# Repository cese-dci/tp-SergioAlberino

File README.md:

# tp-SergioAlberino
tp-SergioAlberino created by GitHub Classroom
Materia: Diseño de Circuitos Impresos. Especialización de Sistemas Embebidos (FIUBA)

Poncho distribuidor para Robot rUVot
====================================

Placa para el robot "rUVot". Se trata de un pequeño robot movil para inspección y desinfección por UV. El mismo tiene un funcionamiento autónomo o puede manejarse en modo teleoperado por Bluetooth

La finalidad de esta Placa es la de cumplir funciones de  "distribuidora" de los pines de la EDU-CIA para interconectar los sensores y actuadores del robot de inspección y desinfección por UV. 
Permite conectar todo en forma ordenada y modular. 
El dongle Bluetooth se conecta a esta placa.

URL: (URL en la wiki de la CIAA)
FUNCIÓN: Placa "distribuidora" de los pines de la EDU-CIA para interconectar los sensores y actuadores de un robot de inspección y desinfección por UV

AUTORES/INSTITUCIONES: Sergio Alberino / GIAR - UTN.FRBA

DOCENTE: Diego Brengi

REVISOR: Pablo D. Folino

Año: 2021

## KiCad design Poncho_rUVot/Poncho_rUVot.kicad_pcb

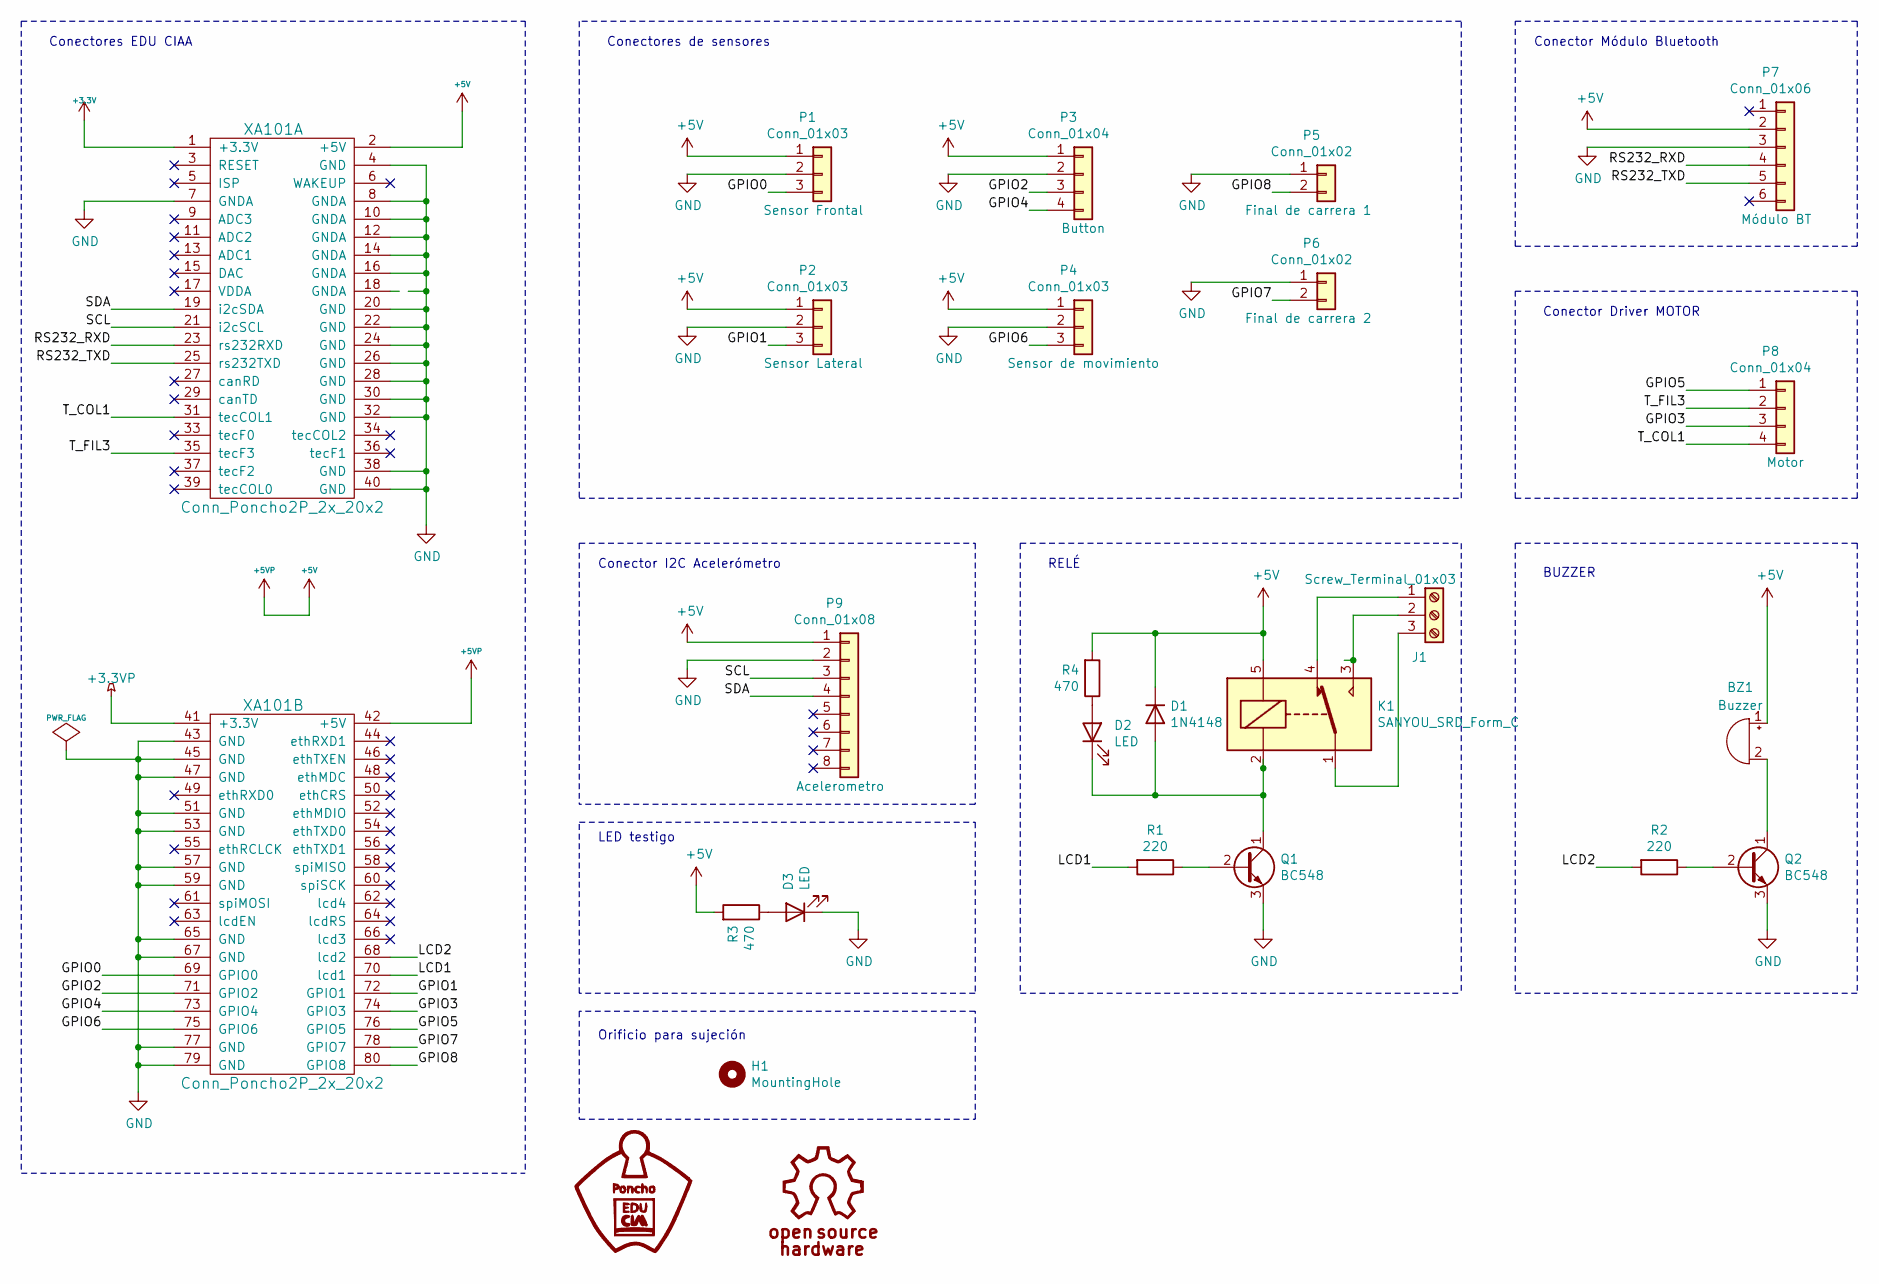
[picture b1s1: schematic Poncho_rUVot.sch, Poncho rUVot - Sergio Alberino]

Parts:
BZ1: Buzzer; Buzzer_12x9.5RM7.6
D1: 1N4148; D_DO-35_SOD27_P10.16mm_Horizontal
D2, D3: LED; LED_D5.0mm
H1: MountingHole; MountingHole_2.5mm
J1: Screw_Terminal_01x03; TerminalBlock_Phoenix_MKDS-1,5-3-5.08_1x03_P5.08mm_Horizont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
K1: SANYOU_SRD_Form_C; Relay_SPDT_SANYOU_SRD_Series_Form_C
P1, P2, P4: Conn_01x03; PinHeader_1x03_P2.54mm_Horizontal
P3: Conn_01x04; PinHeader_1x04_P2.54mm_Horizontal
P5, P6: Conn_01x02; PinHeader_1x02_P2.54mm_Horizontal
P7: Conn_01x06; PinSocket_1x06_P2.54mm_Vertical
P8: Conn_01x04; PinHeader_1x04_P2.54mm_Vertical
P9: Conn_01x08; PinSocket_1x08_P2.54mm_Vertical
Q1, Q2: BC548; TO-92L_Wide
R1, R2: 220; R_Axial_DIN0204_L3.6mm_D1.6mm_P7.62mm_Horizontal
R3, R4: 470; R_Axial_DIN0204_L3.6mm_D1.6mm_P7.62mm_Horizontal
XA101: Conn_Poncho2P_2x_20x2; Conn_Poncho_SinBorde; Digikey# 952-1387-ND

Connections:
+3.3VP: XA101.41 (+3.3V)
+3V3: XA101.1 (+3.3V)
+5V: BZ1.1 (-), D1.1 (K), K1.5, P1.1, P2.1, P3.1, P4.1, P7.2, P9.1, R3.2, R4.2, XA101.2 (+5V), XA101.42 (+5V)
/GPIO0: P1.3, XA101.69 (GPIO0)
/GPIO1: P2.3, XA101.72 (GPIO1)
/GPIO2: P3.3, XA101.71 (GPIO2)
/GPIO3: P8.3, XA101.74 (GPIO3)
/GPIO4: P3.4, XA101.73 (GPIO4)
/GPIO5: P8.1, XA101.76 (GPIO5)
/GPIO6: P4.3, XA101.75 (GPIO6)
/GPIO7: P6.2, XA101.78 (GPIO7)
/GPIO8: P5.2, XA101.80 (GPIO8)
/LCD1: R1.2, XA101.70 (lcd1)
/LCD2: R2.2, XA101.68 (lcd2)
/RS232_RXD: P7.4, XA101.23 (rs232RXD)
/RS232_TXD: P7.5, XA101.25 (rs232TXD)
/SCL: P9.3, XA101.21 (i2cSCL)
/SDA: P9.4, XA101.19 (i2cSDA)
/T_COL1: P8.4, XA101.31 (tecCOL1)
/T_FIL3: P8.2, XA101.35 (tecF3)
GND: D3.1 (K), P1.2, P2.2, P3.2, P4.2, P5.1, P6.1, P7.3, P9.2, Q1.3 (E), Q2.3 (E), XA101.4 (GND), XA101.7 (GNDA), XA101.8 (GNDA), XA101.10 (GNDA), XA101.12 (GNDA), XA101.14 (GNDA), XA101.16 (GNDA), XA101.20 (GND), XA101.22 (GND), XA101.24 (GND), XA101.26 (GND), XA101.28 (GND), XA101.30 (GND), XA101.32 (GND), XA101.38 (GND), XA101.40 (GND), XA101.43 (GND), XA101.45 (GND), XA101.47 (GND), XA101.51 (GND), XA101.53 (GND), XA101.57 (GND), XA101.59 (GND), XA101.65 (GND), XA101.67 (GND), XA101.77 (GND), XA101.79 (GND)
unnamed: BZ1.2 (+), Q2.1 (C)
unnamed: D1.2 (A), D2.1 (K), K1.2, Q1.1 (C)
unnamed: D2.2 (A), R4.1
unnamed: D3.2 (A), R3.1
unnamed: J1.1, K1.4
unnamed: J1.2, K1.3
unnamed: J1.3, K1.1
unnamed: Q1.2 (B), R1.1
unnamed: Q2.2 (B), R2.1

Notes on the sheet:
BUZZER
Conector Módulo Bluetooth
RELÉ
Conector Driver MOTOR
Conector I2C Acelerómetro
Conectores EDU CIAA
Conectores de sensores
LED testigo
Orificio para sujeción

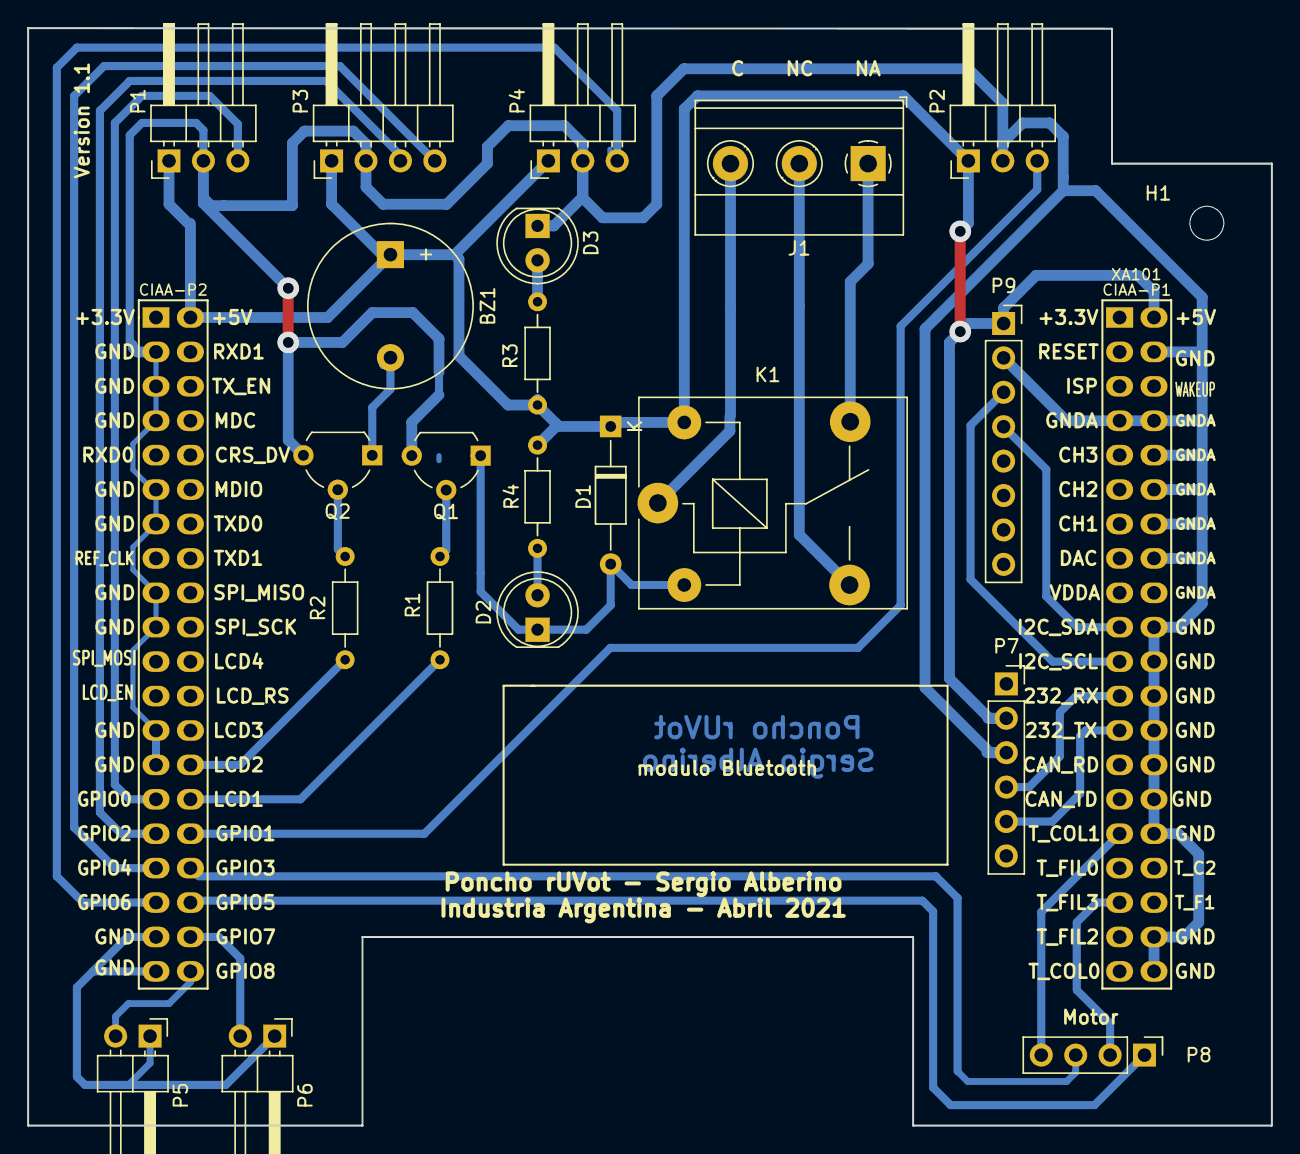
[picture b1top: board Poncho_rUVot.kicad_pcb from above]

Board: 2 copper layers, 91.8 x 81.0 mm, 23 parts (0 on the bottom side), 28 nets.

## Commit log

2021-04-06 Comit inicial
2021-04-06 Se acrualizan archivos carpeta DOC
2021-04-06 actualizo esquematico
2021-04-08 actualización
2021-04-08 Se completa planilla de revisión
2021-04-09 Se elimina erro electrico en esquematico
2021-04-10 actualizacion
2021-04-16 Se hacen correciones indicadas en el esquematico
2021-04-16 posicionamiento
2021-04-20 Se agrega el PCB
2021-04-20 Se agregan detalles
2021-04-21 Correcciones
2021-04-21 Correcciones de tamaño de pista
2021-04-22 Correcciones de detalles
2021-04-22 Agrego Revisión Folino PCB
2021-04-22 Correcciones sugeridas
2021-04-25 Correcciones de PCB sugeridas
2021-04-25 Se elimina un puente
2021-04-26 se agrega led testigo
2021-04-26 Se corrigen detalles
2021-05-13 imagenes
2021-05-14 agrego imagen serigrafia
2021-05-17 Se agregan fotos del proceso de la placa

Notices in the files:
Poncho_rUVot/Poncho_rUVot.kicad_pcb:
Este obra está bajo una licencia de Creative Commons Reconocimiento 4.0 Internacional.
